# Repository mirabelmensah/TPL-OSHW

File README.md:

# Custom Cryogenic Feedthrough

This repository contains the open-source PCB designs for a custom cryogenic feedthrough system developed for the CS204-DMX-20 cryostat.
The hardware is intended for researchers working with photonic devices at cryogenic temperatures, providing a compact, reliable interface between room-temperature electronics and the cryostat interior.

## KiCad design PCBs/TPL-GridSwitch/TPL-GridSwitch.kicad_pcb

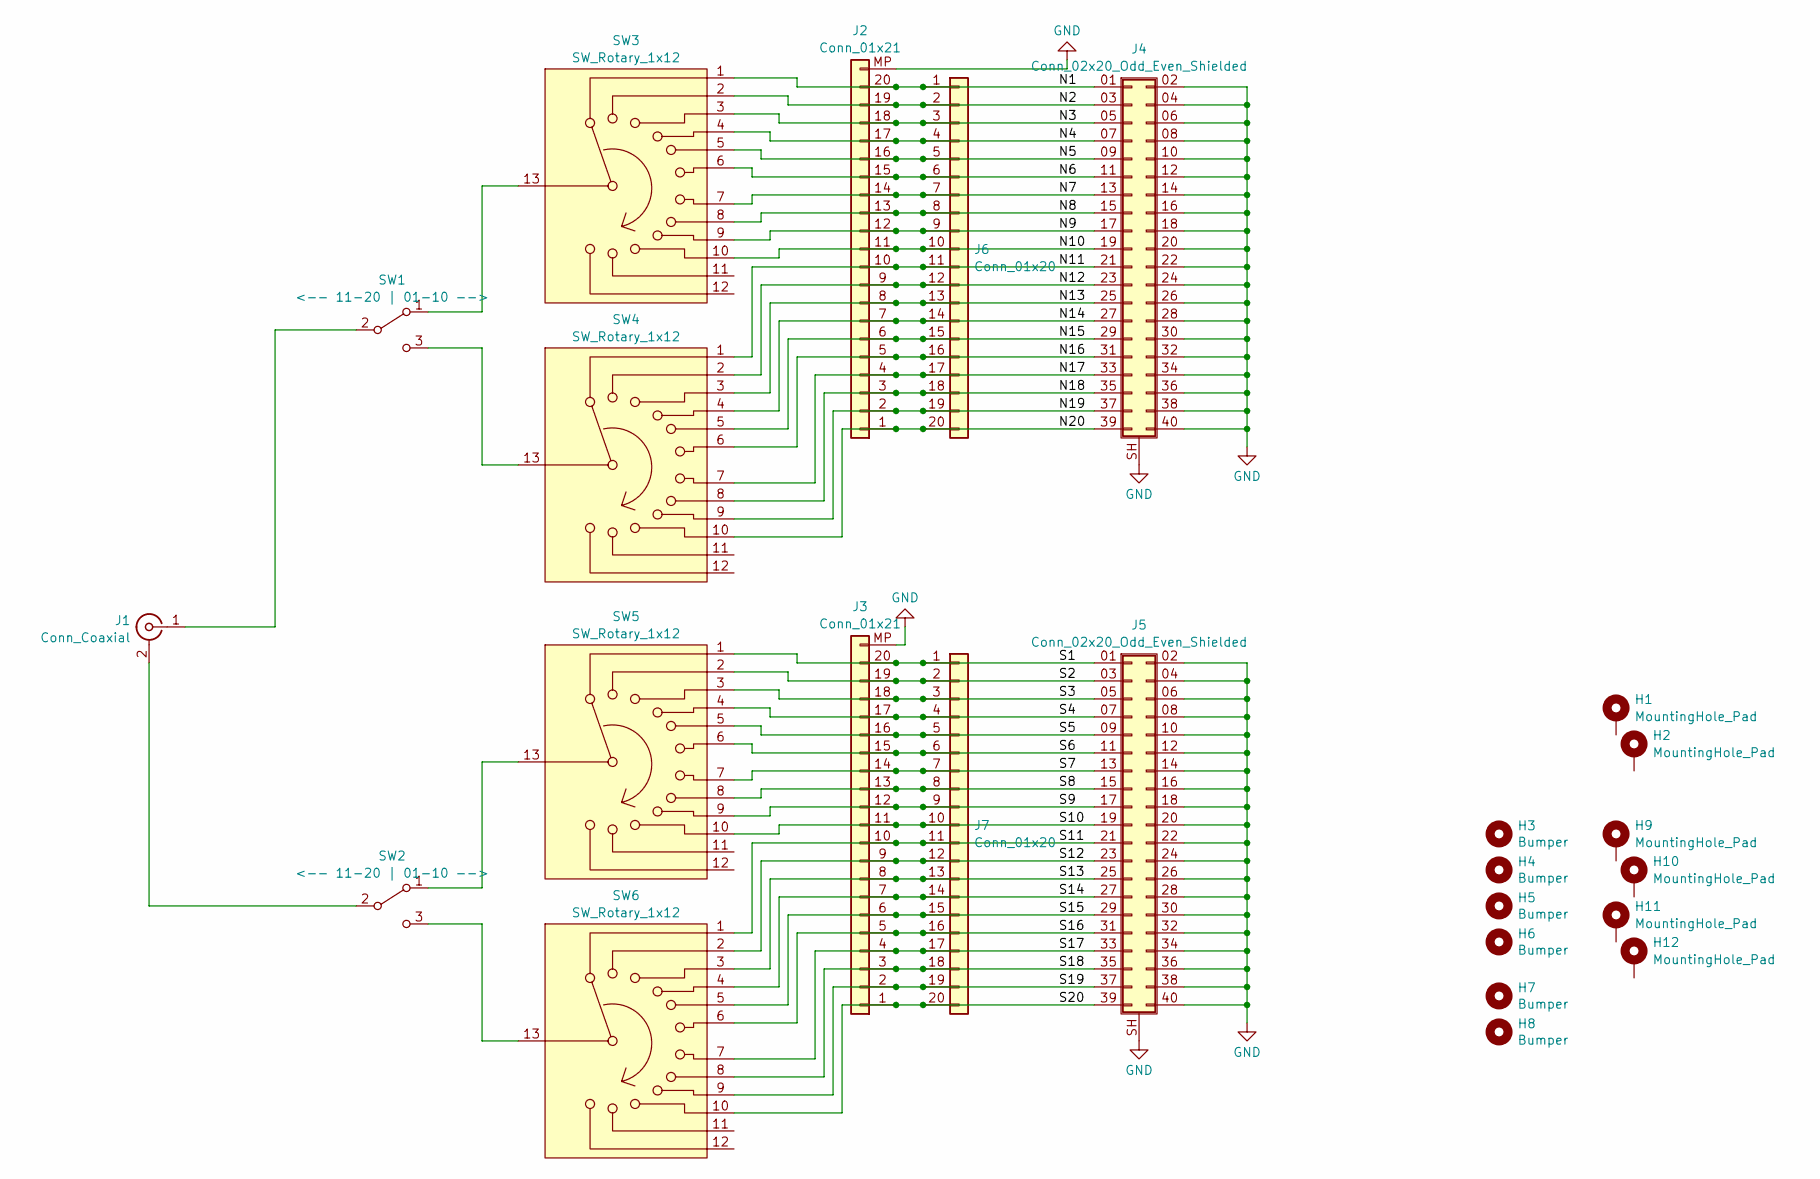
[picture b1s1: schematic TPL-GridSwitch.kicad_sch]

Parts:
H1, H2: MountingHole_Pad; MountingHole_6.4mm_M6_ISO14580_Pad
H3, H4, H5, H6, H7, H8: Bumper; Bumper_SJ5076-oppositeSide; LCSC DNP
H9, H10, H11, H12: MountingHole_Pad; MountingHole_3.5mm_Pad
J1: Conn_Coaxial; BNC_DOSiN-801-0050
J2, J3: Conn_01x21; TE_2-1734839-0_1x20-1MP_P0.5mm_Horizontal
J4, J5: Conn_02x20_Odd_Even_Shielded; LSHM-120-02.5-L-DV-A-S
J6, J7: Conn_01x20; PinHeader_1x20_P2.54mm_Vertical
SW1: <-- 11-20 | 01-10 -->; Toggle-SPDT-Eswitch-100SPxT1B2M2xE
SW2: <-- 11-20 | 01-10 -->; Toggle-SPDT-Eswitch-100SPxT1B2M2xE; LCSC DNP
SW3, SW4, SW5, SW6: SW_Rotary_1x12; SP12T_KC52A30.001NPS

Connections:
/N1: J2.20, J4.01 (Pin_1), J6.1, SW3.1
/N2: J2.19, J4.03 (Pin_3), J6.2, SW3.2
/N3: J2.18, J4.05 (Pin_5), J6.3, SW3.3
/N4: J2.17, J4.07 (Pin_7), J6.4, SW3.4
/N5: J2.16, J4.09 (Pin_9), J6.5, SW3.5
/N6: J2.15, J4.11, J6.6, SW3.6
/N7: J2.14, J4.13, J6.7, SW3.7
/N8: J2.13, J4.15, J6.8, SW3.8
/N9: J2.12, J4.17, J6.9, SW3.9
/N10: J2.11, J4.19, J6.10, SW3.10
/N11: J2.10, J4.21, J6.11, SW4.1
/N12: J2.9, J4.23, J6.12, SW4.2
/N13: J2.8, J4.25, J6.13, SW4.3
/N14: J2.7, J4.27, J6.14, SW4.4
/N15: J2.6, J4.29, J6.15, SW4.5
/N16: J2.5, J4.31, J6.16, SW4.6
/N17: J2.4, J4.33, J6.17, SW4.7
/N18: J2.3, J4.35, J6.18, SW4.8
/N19: J2.2, J4.37, J6.19, SW4.9
/N20: J2.1, J4.39, J6.20, SW4.10
/S1: J3.20, J5.01 (Pin_1), J7.1, SW5.1
/S2: J3.19, J5.03 (Pin_3), J7.2, SW5.2
/S3: J3.18, J5.05 (Pin_5), J7.3, SW5.3
/S4: J3.17, J5.07 (Pin_7), J7.4, SW5.4
/S5: J3.16, J5.09 (Pin_9), J7.5, SW5.5
/S6: J3.15, J5.11, J7.6, SW5.6
/S7: J3.14, J5.13, J7.7, SW5.7
/S8: J3.13, J5.15, J7.8, SW5.8
/S9: J3.12, J5.17, J7.9, SW5.9
/S10: J3.11, J5.19, J7.10, SW5.10
/S11: J3.10, J5.21, J7.11, SW6.1
/S12: J3.9, J5.23, J7.12, SW6.2
/S13: J3.8, J5.25, J7.13, SW6.3
/S14: J3.7, J5.27, J7.14, SW6.4
/S15: J3.6, J5.29, J7.15, SW6.5
/S16: J3.5, J5.31, J7.16, SW6.6
/S17: J3.4, J5.33, J7.17, SW6.7
/S18: J3.3, J5.35, J7.18, SW6.8
/S19: J3.2, J5.37, J7.19, SW6.9
/S20: J3.1, J5.39, J7.20, SW6.10
GND: J2.MP (Pin_21), J3.MP (Pin_21), J4.02 (Pin_2), J4.04 (Pin_4), J4.06 (Pin_6), J4.08 (Pin_8), J4.10, J4.12, J4.14, J4.16, J4.18, J4.20, J4.22, J4.24, J4.26, J4.28, J4.30, J4.32, J4.34, J4.36, J4.38, J4.40, J4.SH (Shield), J5.02 (Pin_2), J5.04 (Pin_4), J5.06 (Pin_6), J5.08 (Pin_8), J5.10, J5.12, J5.14, J5.16, J5.18, J5.20, J5.22, J5.24, J5.26, J5.28, J5.30, J5.32, J5.34, J5.36, J5.38, J5.40, J5.SH (Shield)
unnamed: J1.2 (Ext), SW2.2 (B)
unnamed: J1.1 (In), SW1.2 (B)
unnamed: SW1.1 (A), SW3.13
unnamed: SW1.3 (C), SW4.13
unnamed: SW2.1 (A), SW5.13
unnamed: SW2.3 (C), SW6.13

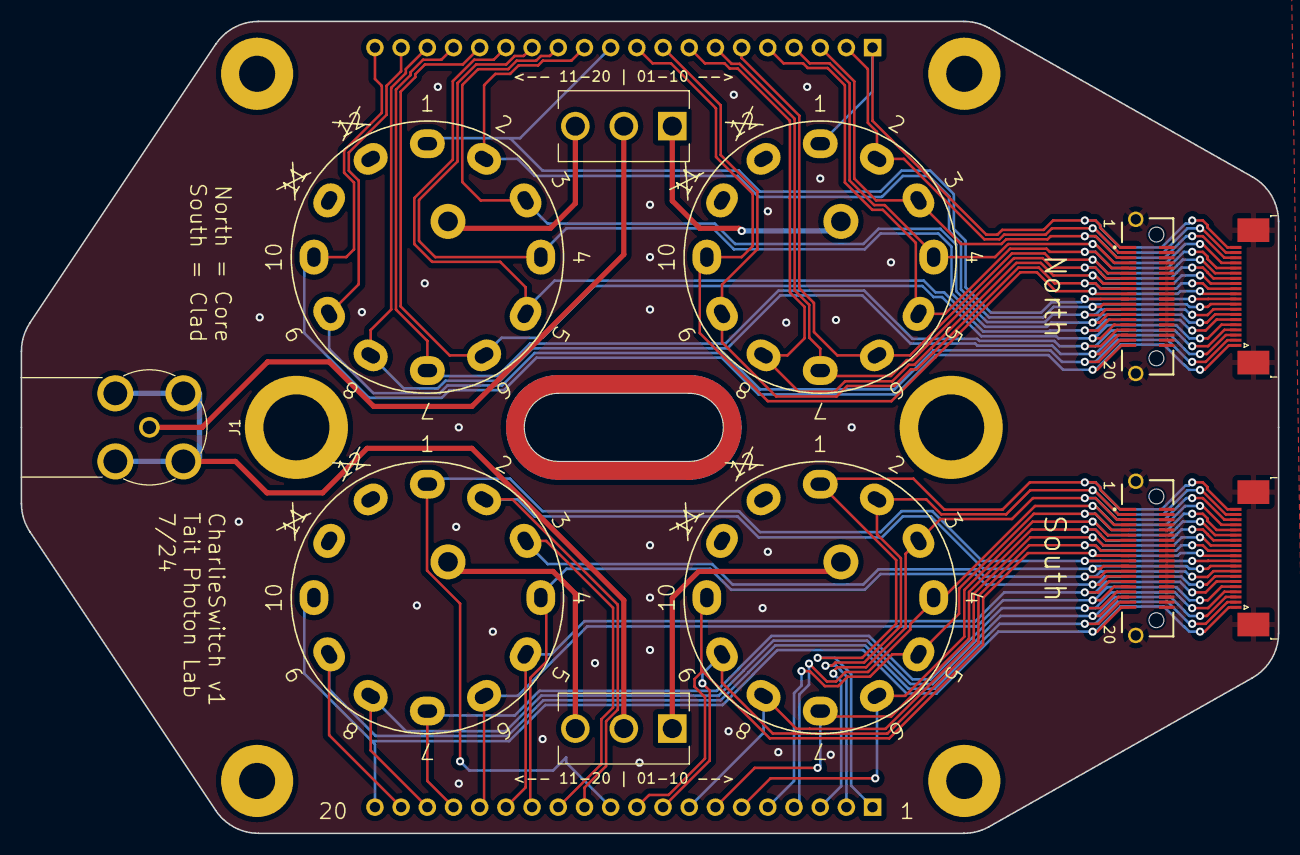
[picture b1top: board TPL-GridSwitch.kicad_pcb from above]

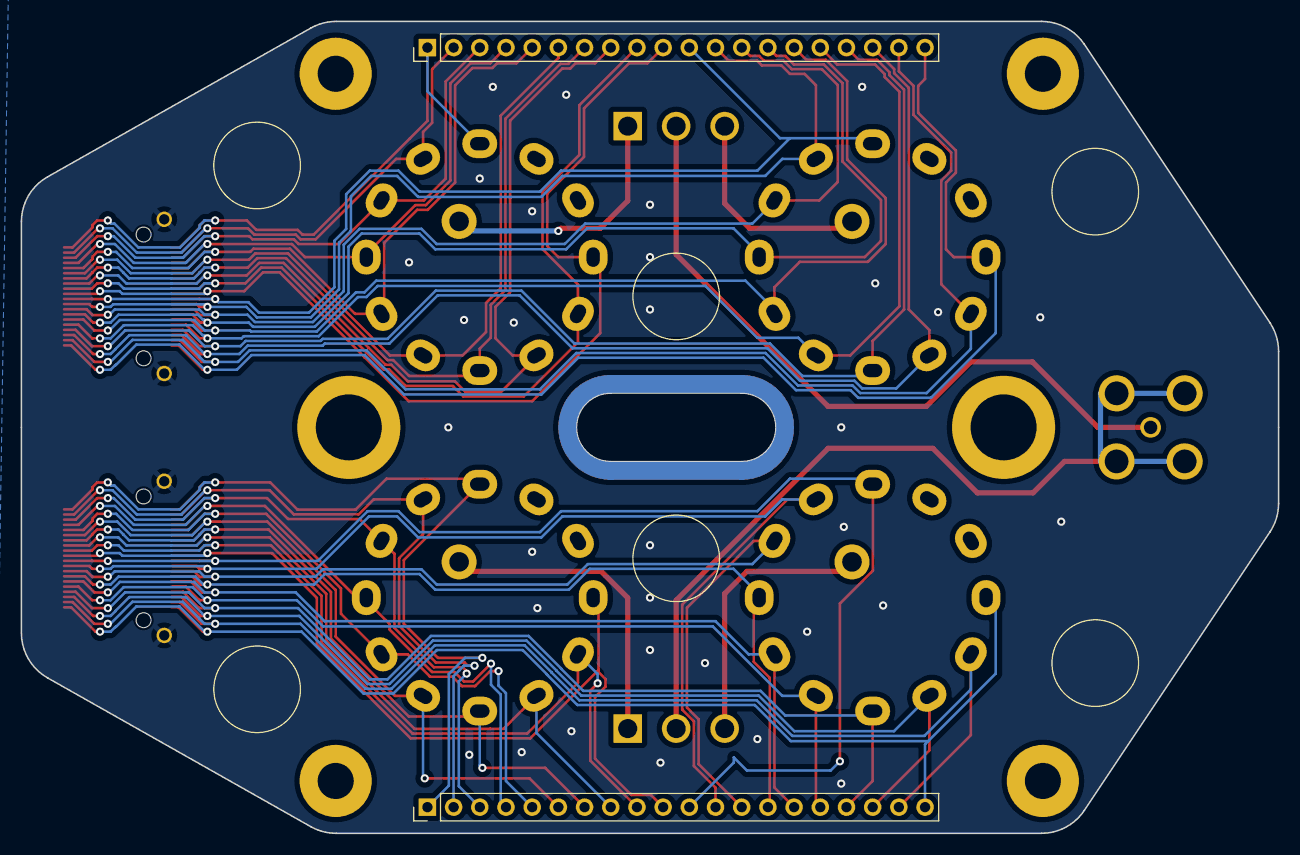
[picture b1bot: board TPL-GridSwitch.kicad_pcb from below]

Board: 2 copper layers, 121.9 x 78.7 mm, 25 parts (2 on the bottom side), 47 nets.

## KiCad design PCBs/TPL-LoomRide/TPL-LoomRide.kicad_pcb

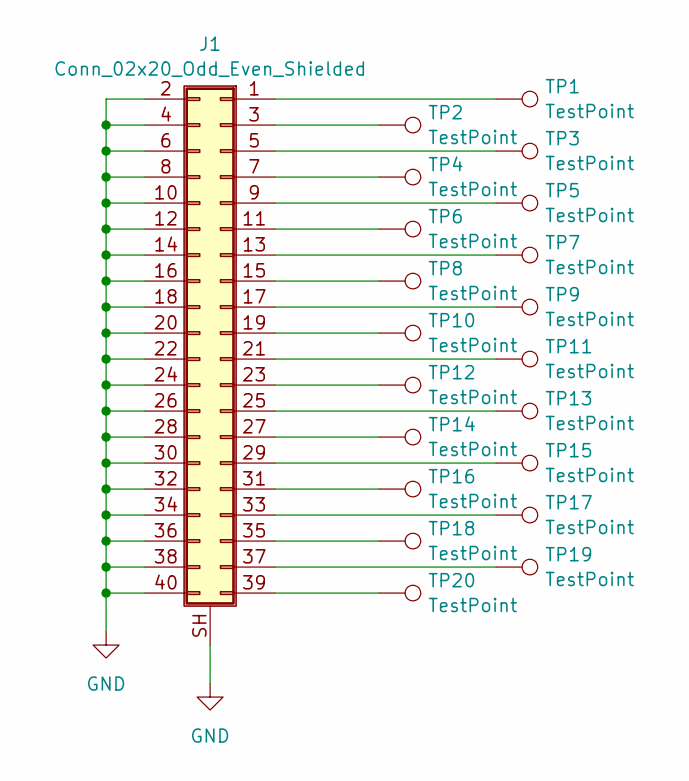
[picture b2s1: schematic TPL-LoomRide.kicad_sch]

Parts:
J1: Conn_02x20_Odd_Even_Shielded; LSHM-120-01-L-DH-A-N
TP1, TP2, TP3, TP4, TP5, TP6, TP7, TP8, TP9, TP10, TP11, TP12, TP13, TP14, TP15, TP16, TP17, TP18, TP19, TP20: TestPoint; WirePoint

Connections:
GND: J1.2, J1.4, J1.6, J1.8, J1.10, J1.12, J1.14, J1.16, J1.18, J1.20, J1.22, J1.24, J1.26, J1.28, J1.30, J1.32, J1.34, J1.36, J1.38, J1.40, J1.SH (Shield)
unnamed: J1.1, TP1.1
unnamed: J1.3, TP2.1
unnamed: J1.5, TP3.1
unnamed: J1.7, TP4.1
unnamed: J1.9, TP5.1
unnamed: J1.11, TP6.1
unnamed: J1.13, TP7.1
unnamed: J1.15, TP8.1
unnamed: J1.17, TP9.1
unnamed: J1.19, TP10.1
unnamed: J1.21, TP11.1
unnamed: J1.23, TP12.1
unnamed: J1.25, TP13.1
unnamed: J1.27, TP14.1
unnamed: J1.29, TP15.1
unnamed: J1.31, TP16.1
unnamed: J1.33, TP17.1
unnamed: J1.35, TP18.1
unnamed: J1.37, TP19.1
unnamed: J1.39, TP20.1

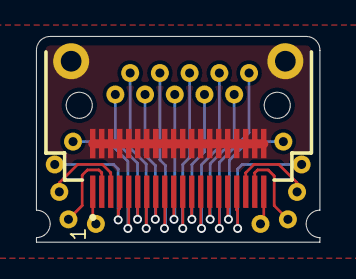
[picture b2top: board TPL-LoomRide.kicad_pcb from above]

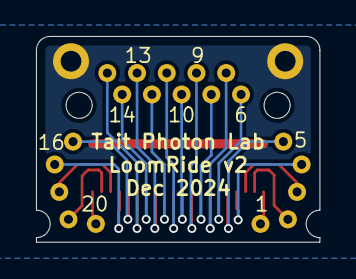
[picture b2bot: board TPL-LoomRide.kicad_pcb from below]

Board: 2 copper layers, 15.7 x 11.4 mm, 21 parts (20 on the bottom side), 21 nets.

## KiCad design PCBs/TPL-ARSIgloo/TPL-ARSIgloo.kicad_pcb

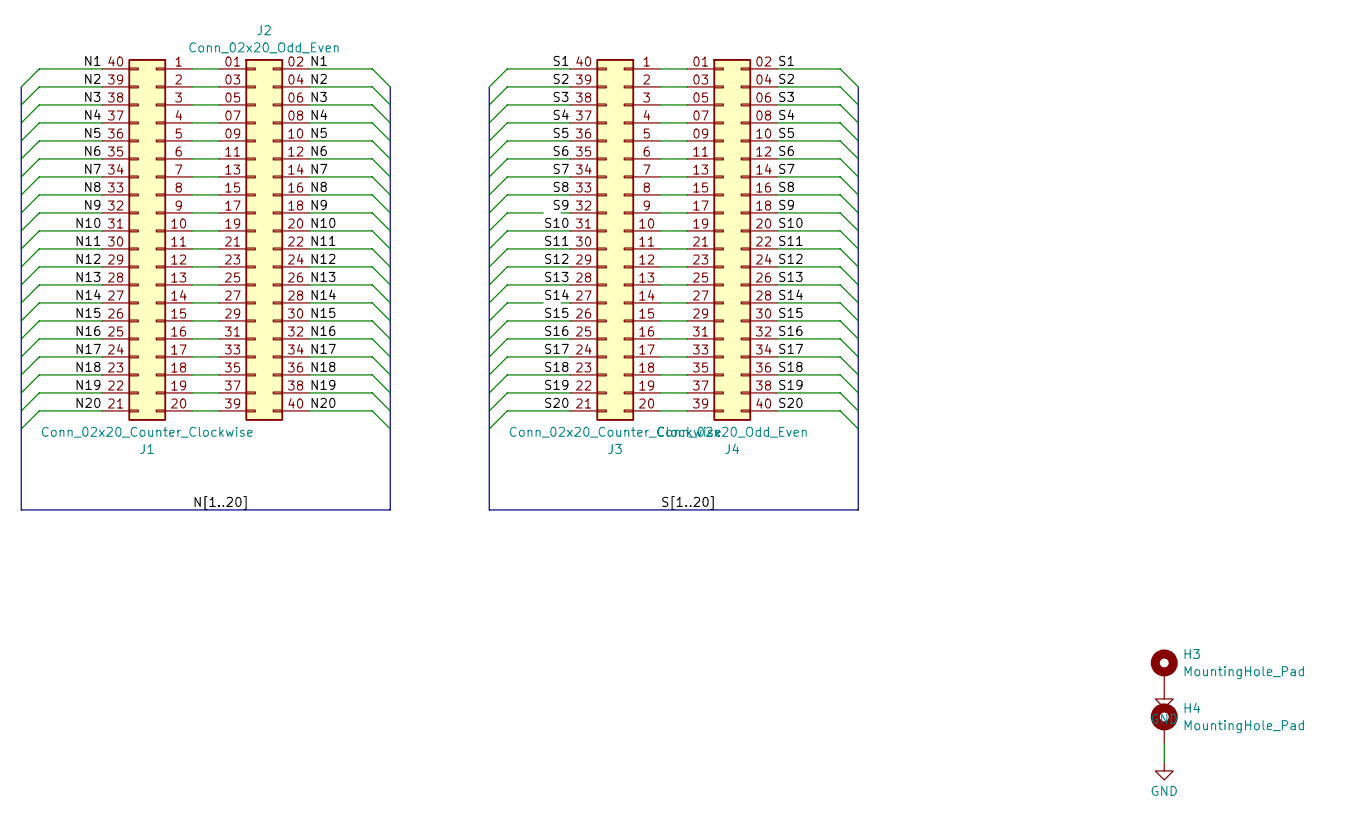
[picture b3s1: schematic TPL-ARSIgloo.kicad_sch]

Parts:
H3, H4: MountingHole_Pad; MountingHole_3.5mm_Pad_TopBottom
J1, J3: Conn_02x20_Counter_Clockwise; WBpadArray-N20-P15-W7-paired
J2, J4: Conn_02x20_Odd_Even; LSHM-120-02.5-L-DV-A-S

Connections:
/N1: J1.40, J2.02 (Pin_2)
/N2: J1.39, J2.04 (Pin_4)
/N3: J1.38, J2.06 (Pin_6)
/N4: J1.37, J2.08 (Pin_8)
/N5: J1.36, J2.10
/N6: J1.35, J2.12
/N7: J1.34, J2.14
/N8: J1.33, J2.16
/N9: J1.32, J2.18
/N10: J1.31, J2.20
/N11: J1.30, J2.22
/N12: J1.29, J2.24
/N13: J1.28, J2.26
/N14: J1.27, J2.28
/N15: J1.26, J2.30
/N16: J1.25, J2.32
/N17: J1.24, J2.34
/N18: J1.23, J2.36
/N19: J1.22, J2.38
/N20: J1.21, J2.40
/S1: J3.40, J4.02 (Pin_2)
/S2: J3.39, J4.04 (Pin_4)
/S3: J3.38, J4.06 (Pin_6)
/S4: J3.37, J4.08 (Pin_8)
/S5: J3.36, J4.10
/S6: J3.35, J4.12
/S7: J3.34, J4.14
/S8: J3.33, J4.16
/S9: J3.32, J4.18
/S10: J3.31, J4.20
/S11: J3.30, J4.22
/S12: J3.29, J4.24
/S13: J3.28, J4.26
/S14: J3.27, J4.28
/S15: J3.26, J4.30
/S16: J3.25, J4.32
/S17: J3.24, J4.34
/S18: J3.23, J4.36
/S19: J3.22, J4.38
/S20: J3.21, J4.40
GND: H3.1, H4.1
unnamed: J1.1, J2.01 (Pin_1)
unnamed: J1.2, J2.03 (Pin_3)
unnamed: J1.3, J2.05 (Pin_5)
unnamed: J1.4, J2.07 (Pin_7)
unnamed: J1.5, J2.09 (Pin_9)
unnamed: J1.6, J2.11
unnamed: J1.7, J2.13
unnamed: J1.8, J2.15
unnamed: J1.9, J2.17
unnamed: J1.10, J2.19
unnamed: J1.11, J2.21
unnamed: J1.12, J2.23
unnamed: J1.13, J2.25
unnamed: J1.14, J2.27
unnamed: J1.15, J2.29
unnamed: J1.16, J2.31
unnamed: J1.17, J2.33
unnamed: J1.18, J2.35
unnamed: J1.19, J2.37
unnamed: J1.20, J2.39
unnamed: J3.1, J4.01 (Pin_1)
unnamed: J3.2, J4.03 (Pin_3)
unnamed: J3.3, J4.05 (Pin_5)
unnamed: J3.4, J4.07 (Pin_7)
unnamed: J3.5, J4.09 (Pin_9)
unnamed: J3.6, J4.11
unnamed: J3.7, J4.13
unnamed: J3.8, J4.15
unnamed: J3.9, J4.17
unnamed: J3.10, J4.19
unnamed: J3.11, J4.21
unnamed: J3.12, J4.23
unnamed: J3.13, J4.25
unnamed: J3.14, J4.27
unnamed: J3.15, J4.29
unnamed: J3.16, J4.31
unnamed: J3.17, J4.33
unnamed: J3.18, J4.35
unnamed: J3.19, J4.37
unnamed: J3.20, J4.39

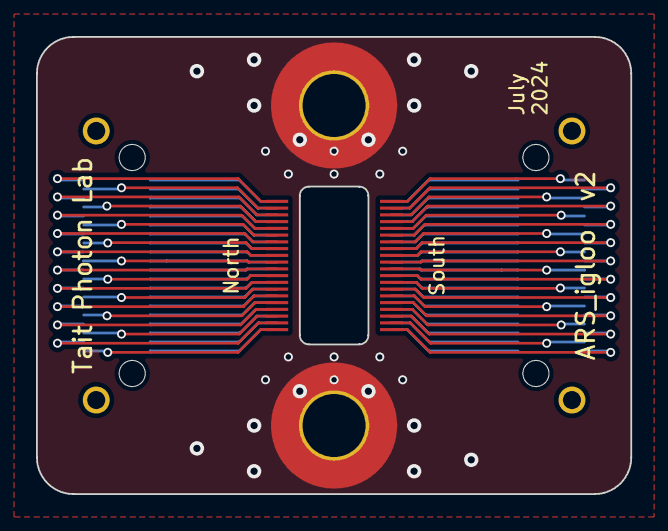
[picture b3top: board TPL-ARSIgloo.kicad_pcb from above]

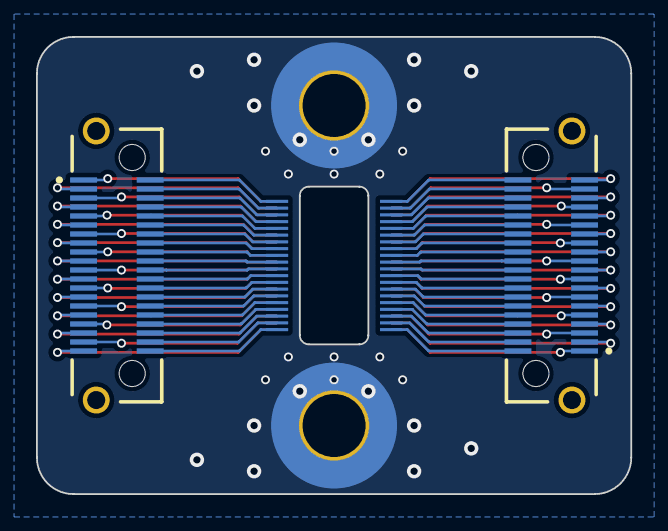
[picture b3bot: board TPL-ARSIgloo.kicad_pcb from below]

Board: 2 copper layers, 33.0 x 25.4 mm, 6 parts (2 on the bottom side), 81 nets.

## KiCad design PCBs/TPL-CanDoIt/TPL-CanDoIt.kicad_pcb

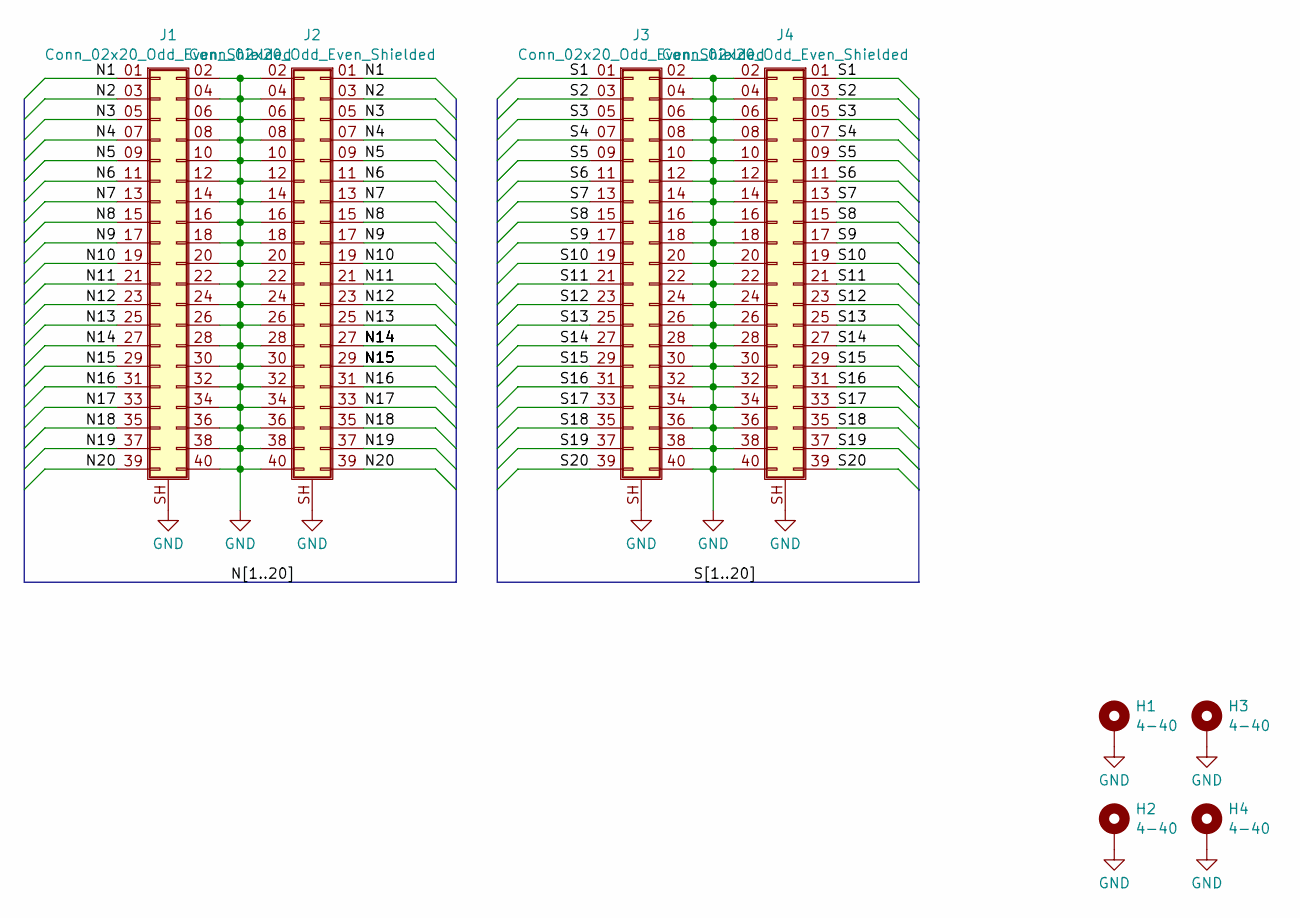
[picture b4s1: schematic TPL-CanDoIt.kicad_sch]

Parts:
H1, H2, H3, H4: 4-40; MountingHole_3.7mm
J1, J3: Conn_02x20_Odd_Even_Shielded; LSHM-120-02.5-L-DV-A-S
J2, J4: Conn_02x20_Odd_Even_Shielded; LSHM-120-01-L-RH-A-S

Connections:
/N1: J1.01 (Pin_1), J2.01 (Pin_1)
/N2: J1.03 (Pin_3), J2.03 (Pin_3)
/N3: J1.05 (Pin_5), J2.05 (Pin_5)
/N4: J1.07 (Pin_7), J2.07 (Pin_7)
/N5: J1.09 (Pin_9), J2.09 (Pin_9)
/N6: J1.11, J2.11
/N7: J1.13, J2.13
/N8: J1.15, J2.15
/N9: J1.17, J2.17
/N10: J1.19, J2.19
/N11: J1.21, J2.21
/N12: J1.23, J2.23
/N13: J1.25, J2.25
/N14: J1.27, J2.27
/N15: J1.29, J2.29
/N16: J1.31, J2.31
/N17: J1.33, J2.33
/N18: J1.35, J2.35
/N19: J1.37, J2.37
/N20: J1.39, J2.39
/S1: J3.01 (Pin_1), J4.01 (Pin_1)
/S2: J3.03 (Pin_3), J4.03 (Pin_3)
/S3: J3.05 (Pin_5), J4.05 (Pin_5)
/S4: J3.07 (Pin_7), J4.07 (Pin_7)
/S5: J3.09 (Pin_9), J4.09 (Pin_9)
/S6: J3.11, J4.11
/S7: J3.13, J4.13
/S8: J3.15, J4.15
/S9: J3.17, J4.17
/S10: J3.19, J4.19
/S11: J3.21, J4.21
/S12: J3.23, J4.23
/S13: J3.25, J4.25
/S14: J3.27, J4.27
/S15: J3.29, J4.29
/S16: J3.31, J4.31
/S17: J3.33, J4.33
/S18: J3.35, J4.35
/S19: J3.37, J4.37
/S20: J3.39, J4.39
GND: H1.1, H2.1, H3.1, H4.1, J1.02 (Pin_2), J1.04 (Pin_4), J1.06 (Pin_6), J1.08 (Pin_8), J1.10, J1.12, J1.14, J1.16, J1.18, J1.20, J1.22, J1.24, J1.26, J1.28, J1.30, J1.32, J1.34, J1.36, J1.38, J1.40, J1.SH (Shield), J2.02 (Pin_2), J2.04 (Pin_4), J2.06 (Pin_6), J2.08 (Pin_8), J2.10, J2.12, J2.14, J2.16, J2.18, J2.20, J2.22, J2.24, J2.26, J2.28, J2.30, J2.32, J2.34, J2.36, J2.38, J2.40, J2.SH (Shield), J3.02 (Pin_2), J3.04 (Pin_4), J3.06 (Pin_6), J3.08 (Pin_8), J3.10, J3.12, J3.14, J3.16, J3.18, J3.20, J3.22, J3.24, J3.26, J3.28, J3.30, J3.32, J3.34, J3.36, J3.38, J3.40, J3.SH (Shield), J4.02 (Pin_2), J4.04 (Pin_4), J4.06 (Pin_6), J4.08 (Pin_8), J4.10, J4.12, J4.14, J4.16, J4.18, J4.20, J4.22, J4.24, J4.26, J4.28, J4.30, J4.32, J4.34, J4.36, J4.38, J4.40, J4.SH (Shield)

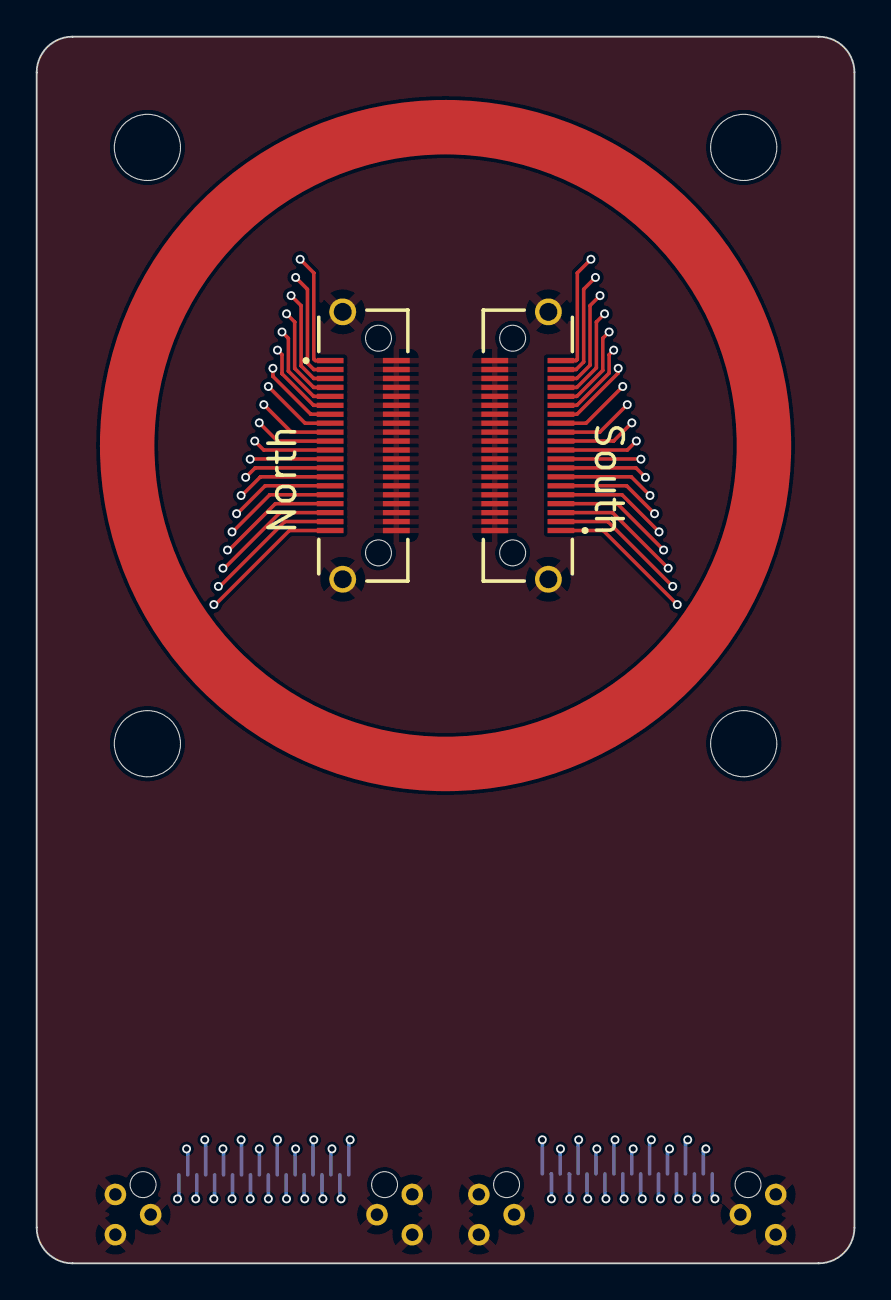
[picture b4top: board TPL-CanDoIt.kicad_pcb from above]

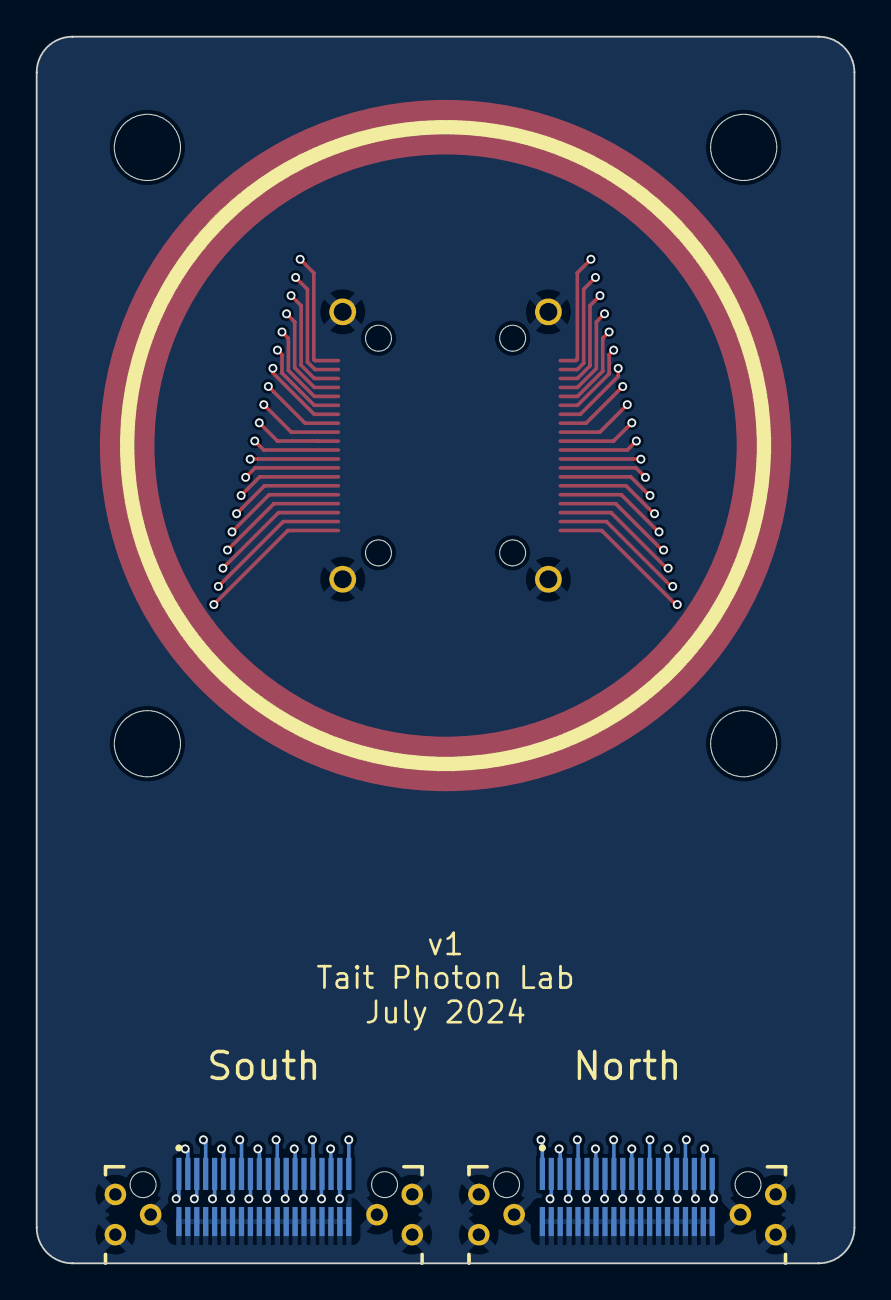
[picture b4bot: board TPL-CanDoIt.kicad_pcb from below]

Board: 4 copper layers, 45.7 x 68.6 mm, 8 parts (2 on the bottom side), 41 nets.

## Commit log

2025-12-07 CanDoIt cryostat feedthrough
2025-12-07 Add Igloo mount PCB with 20 pads
2025-12-07 Add the cable breakout LoomRide
2025-12-07 Add GridSwitch
2025-12-08 Add citation for repo
